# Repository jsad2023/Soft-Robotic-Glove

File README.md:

# Soft-Robotic-Glove
GitHub Repository for Boston University Senior Design Group Soft Robotic Glove for Active Resistance Hand Rehabilitation.

Contributors:
Tessa Johnson, Justin Sadler, Caroline Leilani Stevenson, Megan Le, Thomas Murillo. 

Project based on research from Leah Geata and Professor Tommaso Ranzani at Boston University's Morphable Biorobotics Lab

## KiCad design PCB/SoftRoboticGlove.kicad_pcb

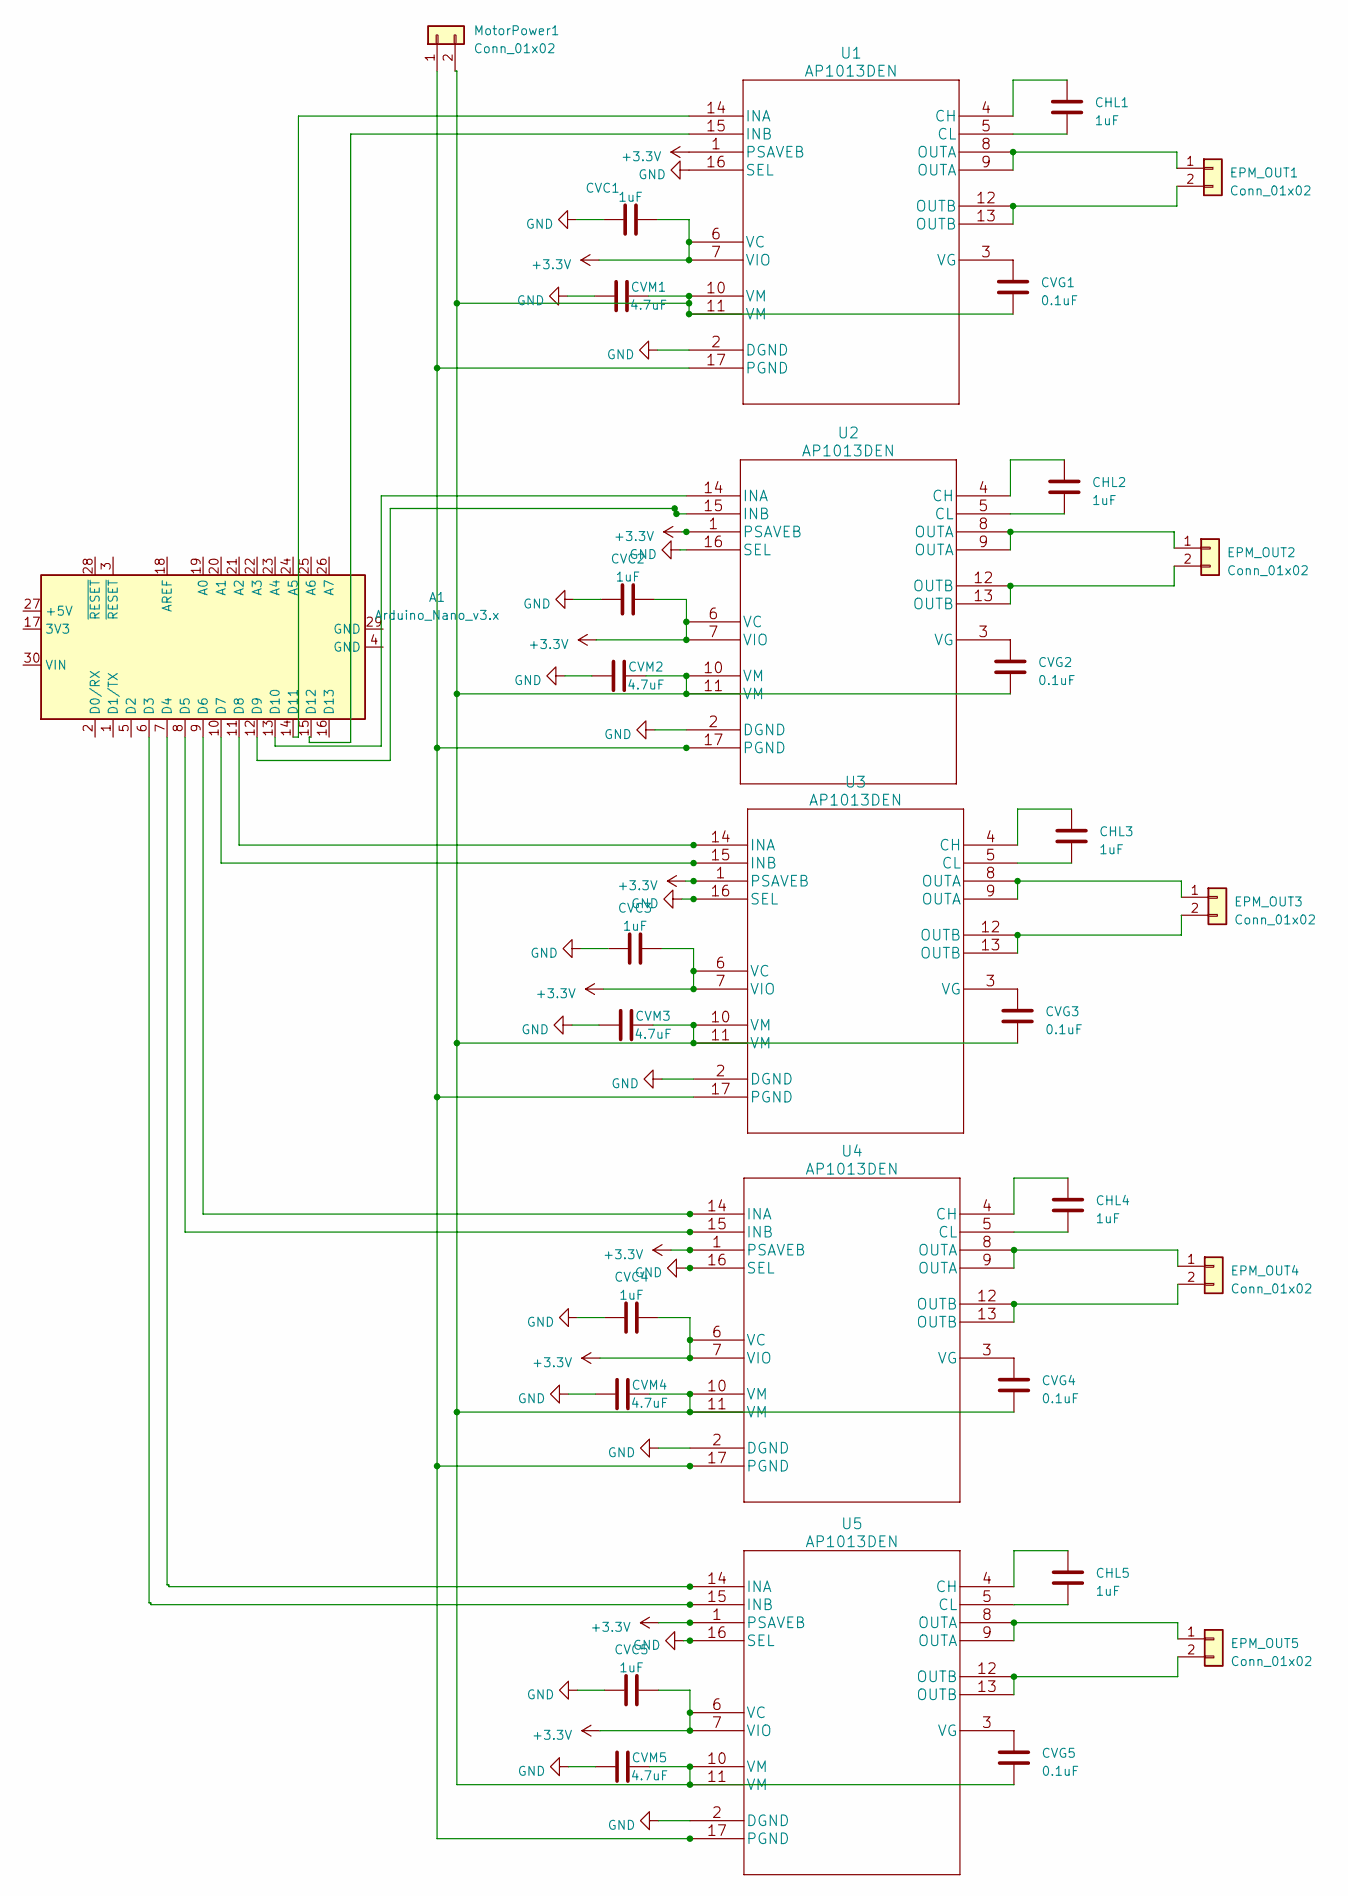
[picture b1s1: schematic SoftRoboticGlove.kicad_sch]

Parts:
A1: Arduino_Nano_v3.x; Arduino_Nano
CHL1, CHL2, CHL3, CHL4, CHL5: 1uF; CP_Axial_L10.0mm_D4.5mm_P15.00mm_Horizontal
CVC1, CVC2, CVC3, CVC4, CVC5: 1uF; CP_Axial_L10.0mm_D4.5mm_P15.00mm_Horizontal
CVG1, CVG2, CVG3, CVG4, CVG5: 0.1uF; CP_Axial_L10.0mm_D4.5mm_P15.00mm_Horizontal
CVM1, CVM2, CVM3, CVM4, CVM5: 4.7uF; CP_Axial_L10.0mm_D4.5mm_P15.00mm_Horizontal
EPM_OUT1, EPM_OUT2, EPM_OUT3, EPM_OUT4, EPM_OUT5: Conn_01x02; SolderWire-0.1sqmm_1x02_P3.6mm_D0.4mm_OD1mm
MotorPower1: Conn_01x02; SolderWire-0.1sqmm_1x02_P3.6mm_D0.4mm_OD1mm
U1, U2, U3, U4, U5: AP1013DEN

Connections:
+3.3V: CVC1.2, CVC2.2, CVC3.2, CVC4.2, CVC5.2, U1.1 (PSAVEB), U1.6 (VC), U1.7 (VIO), U2.1 (PSAVEB), U2.6 (VC), U2.7 (VIO), U3.1 (PSAVEB), U3.6 (VC), U3.7 (VIO), U4.1 (PSAVEB), U4.6 (VC), U4.7 (VIO), U5.1 (PSAVEB), U5.6 (VC), U5.7 (VIO)
GND: CVC1.1, CVC2.1, CVC3.1, CVC4.1, CVC5.1, CVM1.1, CVM2.1, CVM3.1, CVM4.1, CVM5.1, U1.2 (DGND), U1.16 (SEL), U2.2 (DGND), U2.16 (SEL), U3.2 (DGND), U3.16 (SEL), U4.2 (DGND), U4.16 (SEL), U5.2 (DGND), U5.16 (SEL)
unnamed: A1.6 (D3), U5.15 (INB)
unnamed: A1.7 (D4), U5.14 (INA)
unnamed: A1.8 (D5), U4.15 (INB)
unnamed: A1.9 (D6), U4.14 (INA)
unnamed: A1.10 (D7), U3.15 (INB)
unnamed: A1.11 (D8), U3.14 (INA)
unnamed: A1.12 (D9), U2.15 (INB)
unnamed: A1.13 (D10), U2.14 (INA)
unnamed: A1.14 (D11), U1.14 (INA)
unnamed: A1.15 (D12), U1.15 (INB)
unnamed: CVG3.2, CVM3.2, U3.10 (VM), U3.11 (VM)
unnamed: EPM_OUT1.1, U1.8 (OUTA), U1.9 (OUTA)
unnamed: EPM_OUT1.2, U1.12 (OUTB), U1.13 (OUTB)
unnamed: EPM_OUT2.1, U2.8 (OUTA), U2.9 (OUTA)
unnamed: EPM_OUT2.2, U2.12 (OUTB), U2.13 (OUTB)
unnamed: EPM_OUT3.1, U3.8 (OUTA), U3.9 (OUTA)
unnamed: EPM_OUT3.2, U3.12 (OUTB), U3.13 (OUTB)
unnamed: EPM_OUT4.1, U4.8 (OUTA), U4.9 (OUTA)
unnamed: EPM_OUT4.2, U4.12 (OUTB), U4.13 (OUTB)
unnamed: EPM_OUT5.1, U5.8 (OUTA), U5.9 (OUTA)
unnamed: EPM_OUT5.2, U5.12 (OUTB), U5.13 (OUTB)
unnamed: MotorPower1.1, U1.17 (PGND), U2.17 (PGND), U3.17 (PGND), U4.17 (PGND), U5.17 (PGND)
unnamed: CVG1.2, CVG2.2, CVG4.2, CVG5.2, CVM1.2, CVM2.2, CVM4.2, CVM5.2, MotorPower1.2, U1.10 (VM), U1.11 (VM), U2.10 (VM), U2.11 (VM), U4.10 (VM), U4.11 (VM), U5.10 (VM), U5.11 (VM)
unnamed: CHL1.1, U1.4 (CH)
unnamed: CHL1.2, U1.5 (CL)
unnamed: CVG1.1, U1.3 (VG)
unnamed: CHL2.1, U2.4 (CH)
unnamed: CHL2.2, U2.5 (CL)
unnamed: CVG2.1, U2.3 (VG)
unnamed: CHL3.1, U3.4 (CH)
unnamed: CHL3.2, U3.5 (CL)
unnamed: CVG3.1, U3.3 (VG)
unnamed: CHL4.1, U4.4 (CH)
unnamed: CHL4.2, U4.5 (CL)
unnamed: CVG4.1, U4.3 (VG)
unnamed: CHL5.1, U5.4 (CH)
unnamed: CHL5.2, U5.5 (CL)
unnamed: CVG5.1, U5.3 (VG)

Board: 2 copper layers, 32 parts (0 on the bottom side), 40 nets, no tracks yet.

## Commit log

2022-12-05 Included contributors
2023-02-24 Create Arduino
2023-02-24 Added sketch of controlling LED via Bluetooth

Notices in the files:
parts and their libraries:
Copyright 2021 Accelerated Designs. All rights reserved.
